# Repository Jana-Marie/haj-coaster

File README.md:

# haj-coaster

A sharky and colourful coaster glowing in pride for you~.

It consists of a stack of three circuit boards, sandwhiched together. There is a STM32F072, a LED driver and plenty LEDs on the baseboard, cutouts on the midboards to hide the components in, and a mask frontboard that shows the artwork. The LEDs are not all simple RGB ones, but a set of single color LEDs for the stars, carefully selected to represent the diversity in color on a night sky. For the girl on the left side, each LED spot consists of 5 single LEDs, RGB + Pink + Cyan, allowing one to expand the typical RGB range with opically pleasant cyan tones (for the shark and drink) and pink tones (e.g. for the skin, shark and drink).
There is also a NTC within the stack, I intended to change the sharks colour from cyan to pink following the coasters temperature. A warm drink would tint the shark pink, a cold one cyan. However, I never dared to place a drink on it, it's just to cute to hide it behind some glass or mug 🥺

<table>
  <tbody>
    <tr>
      <td colspan="2">
        
      </td>
    </tr>
    <tr>
      <td>
        
      </td>
      <td>
        
      </td>
    </tr>
    <tr>
      <td colspan="2">
        
      </td>
    </tr>
    <tr>
      <td>
        
      </td>
      <td>
        
      </td>
    </tr>
    <tr>
      <td colspan="2">
        
      </td>
    </tr>
  </tbody>
</table>

---

### Schematic

(https://github.com/Jana-Marie/haj-coaster/blob/main/coaster_backboard/schematic.pdf)[schematic.pdf]

---

Thank you [かにあじ](https://void-aquarium.com/) for allowing me to use your fantastic artwork for this project! ありがとうございます!

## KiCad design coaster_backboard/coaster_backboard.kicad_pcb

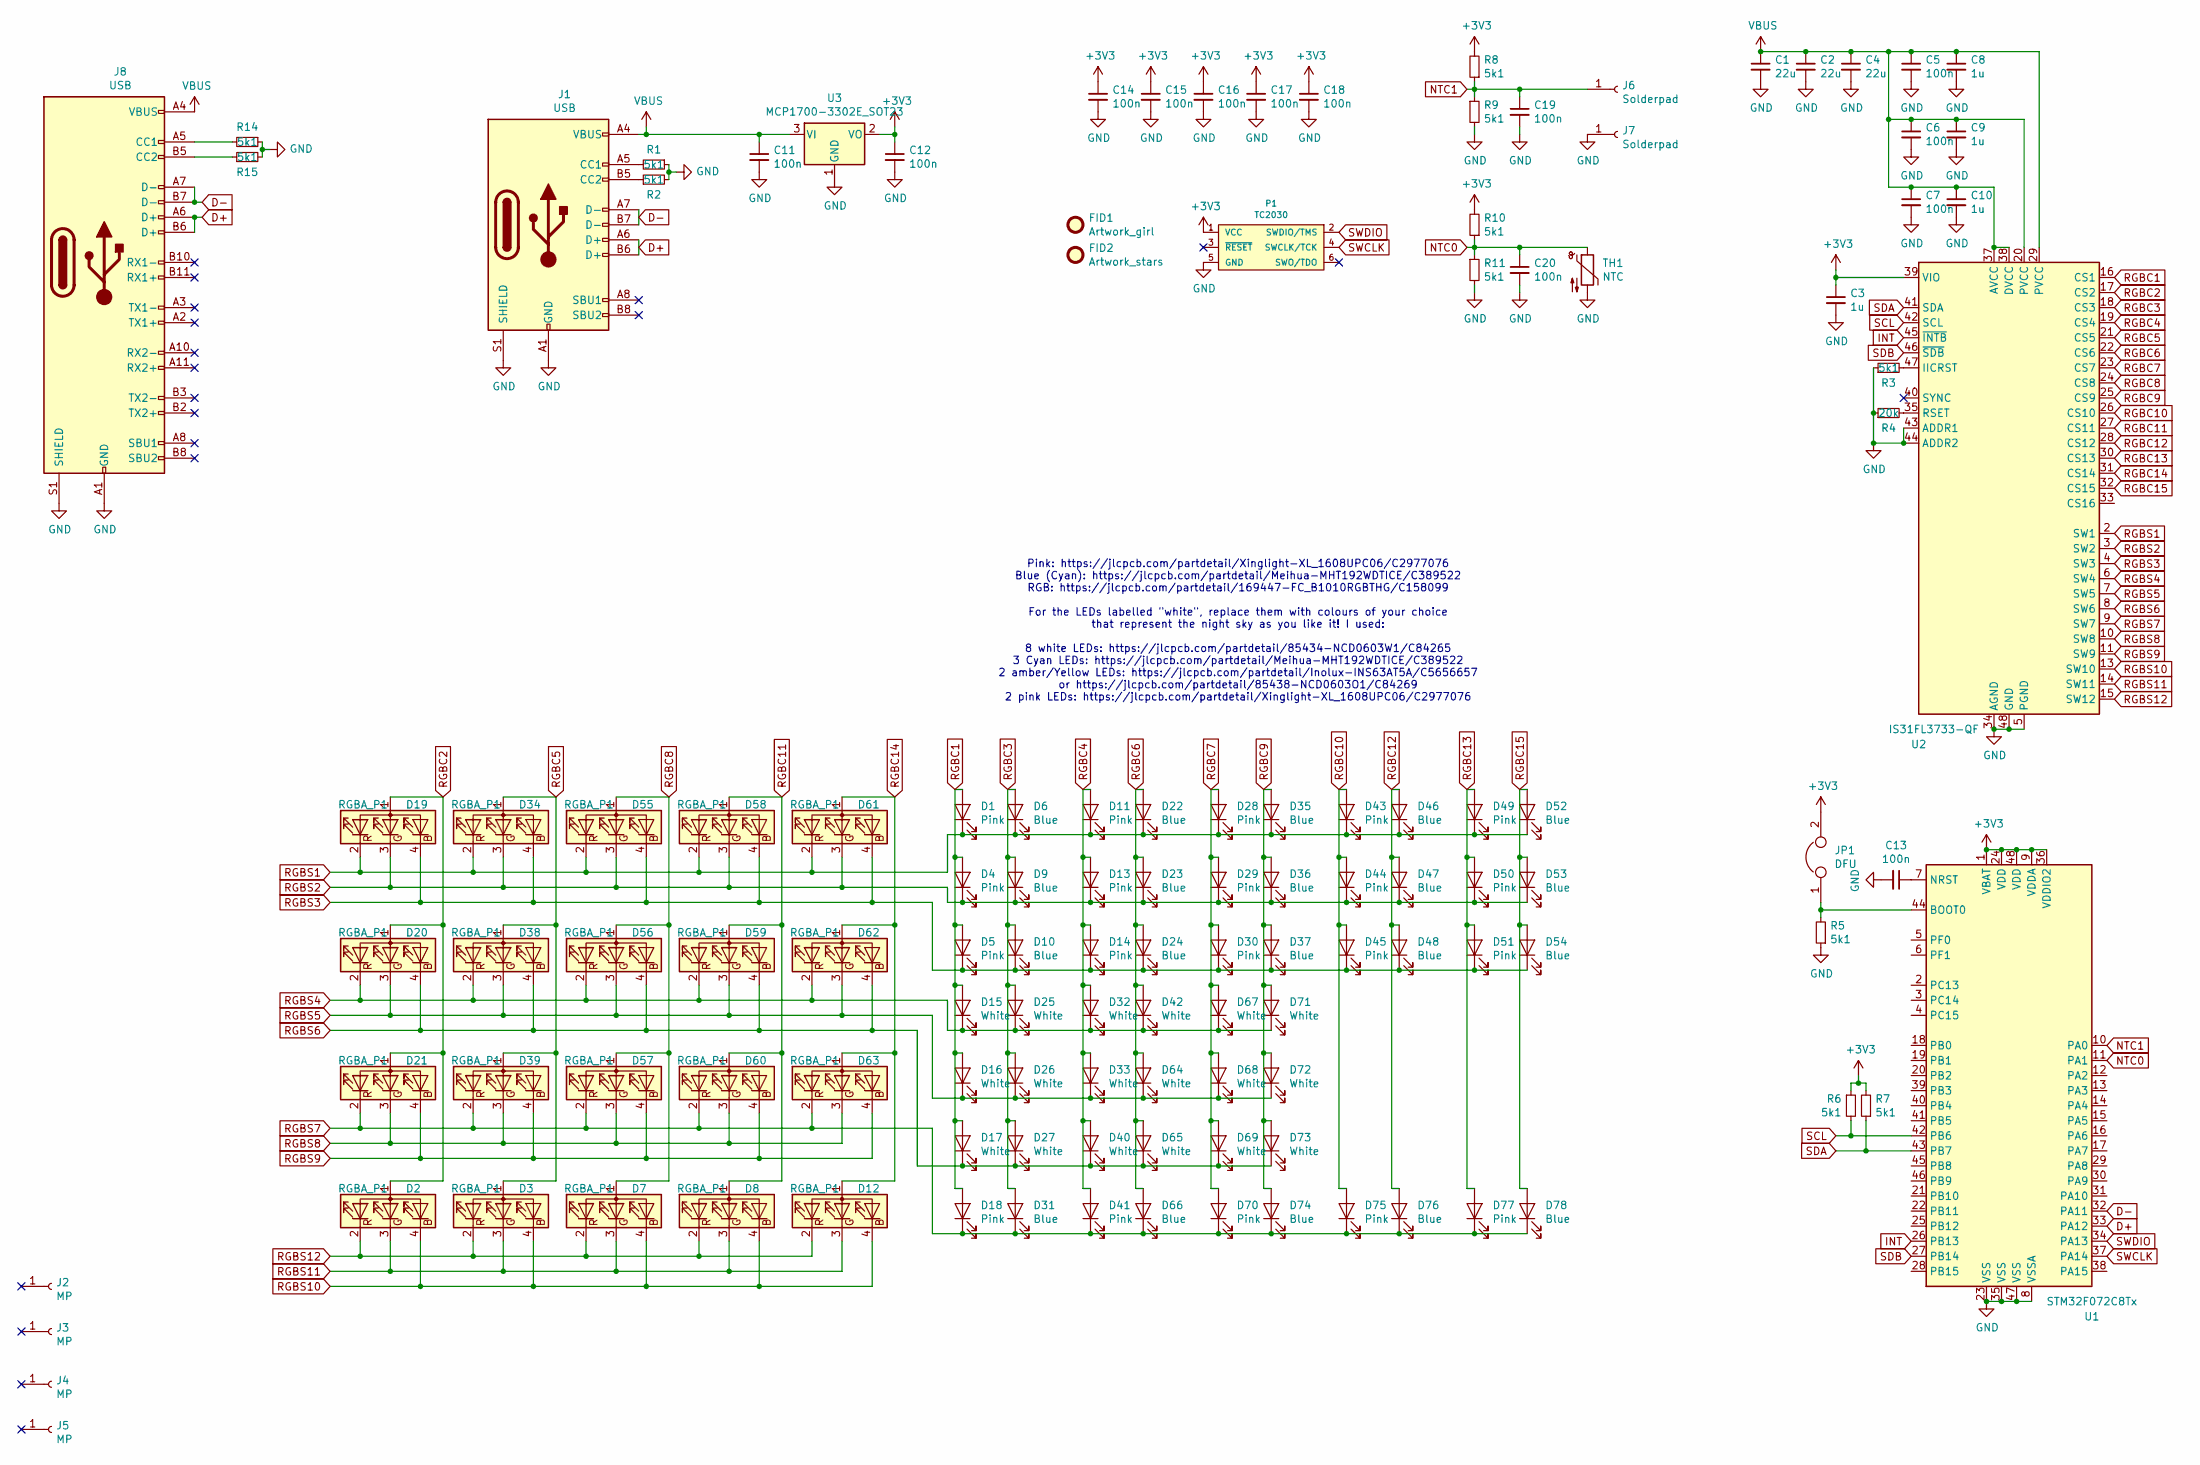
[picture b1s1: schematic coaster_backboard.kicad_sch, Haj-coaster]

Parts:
C1, C2, C4: 22u; C_0805
C3, C8, C9, C10: 1u; C_0603
C5, C6, C7, C11, C12, C13, C14, C15, C16, C17, C18, C19, C20: 100n; C_0402
D1, D4, D5, D11, D13, D14, D18, D28, D29, D30, D41, D43, D44, D45, D49, D50, D51, D70, D75, D77: Pink; LED_0603_1608Metric
D2, D3, D7, D8, D12, D19, D20, D21, D34, D38, D39, D55, D56, D57, D58, D59, D60, D61, D62, D63: RGBA_P1; FC-B1010RGBT-HG
D6, D9, D10, D22, D23, D24, D31, D35, D36, D37, D46, D47, D48, D52, D53, D54, D66, D74, D76, D78: Blue; LED_0603_1608Metric
D15, D16, D17, D25, D26, D27, D32, D33, D40, D42, D64, D65, D67, D68, D69, D71, D72, D73: White; LED_0603_1608Metric
FID1: Artwork_girl; shark_girl_kani_aji_
FID2: Artwork_stars; stars_kani_aji_
J1: USB; USB-C 16Pin InBoard
J2, J3, J4, J5: MP; Pin_D1.0mm_L10.0mm_LooseFit
J6, J7: Solderpad; Pin_D0.7mm_L6.5mm_W1.8mm_FlatFork
J8: USB; 918-418K2022Y40004
JP1: DFU; R_0805
P1: TC2030
R1, R2, R3, R5, R6, R7, R8, R9, R10, R11, R14, R15: 5k1; R_0402
R4: 20k; R_0402
TH1: NTC; R_0603
U1: STM32F072C8Tx; LQFP-48_7x7mm_P0.5mm
U2: IS31FL3733-QF; QFN-48-1EP_6x6mm_P0.4mm_EP4.2x4.2mm
U3: MCP1700-3302E_SOT23; SOT-23

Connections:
+3V3: C3.1, C12.1, C14.1, C15.1, C16.1, C17.1, C18.1, JP1.2, P1.1 (VCC), R6.1, R7.2, R8.2, R10.2, U1.1 (VBAT), U1.9 (VDDA), U1.24 (VDD), U1.36 (VDDIO2), U1.48 (VDD), U2.39 (VIO), U3.2 (VO)
D+: J1.A6 (D+), J1.B6 (D+), J8.A6 (D+), J8.B6 (D+), U1.33 (PA12)
D-: J1.A7 (D-), J1.B7 (D-), J8.A7 (D-), J8.B7 (D-), U1.32 (PA11)
GND: C1.2, C2.2, C3.2, C4.2, C5.2, C6.2, C7.2, C8.2, C9.2, C10.2, C11.2, C12.2, C13.2, C14.2, C15.2, C16.2, C17.2, C18.2, C19.2, C20.2, J1.A1 (GND), J1.A12 (GND), J1.B1 (GND), J1.B12 (GND), J1.S1 (SHIELD), J7.1, J8.A1 (GND), J8.A12 (GND), J8.B1 (GND), J8.B12 (GND), J8.S1 (SHIELD), P1.5 (GND), R1.1, R2.2, R3.1, R4.1, R5.1, R9.2, R11.2, R14.1, R15.2, TH1.2, U1.8 (VSSA), U1.23 (VSS), U1.35 (VSS), U1.47 (VSS), U2.5 (PGND), U2.12 (PGND), U2.34 (AGND), U2.43 (ADDR1), U2.44 (ADDR2), U2.48 (GND), U2.49 (GND), U3.1 (GND)
INT: U1.26 (PB13), U2.45 (~INTB)
NTC0: C20.1, R10.1, R11.1, TH1.1, U1.11 (PA1)
NTC1: C19.1, J6.1, R8.1, R9.1, U1.10 (PA0)
unnamed: C13.1, U1.7 (NRST)
unnamed: J1.A5 (CC1), R1.2
unnamed: J1.B5 (CC2), R2.1
unnamed: J8.A5 (CC1), R14.2
unnamed: J8.B5 (CC2), R15.1
unnamed: JP1.1, R5.2, U1.44 (BOOT0)
unnamed: R3.2, U2.47 (IICRST)
unnamed: R4.2, U2.35 (RSET)
RGBC1: D1.2 (A), D4.2 (A), D5.2 (A), D15.2 (A), D16.2 (A), D17.2 (A), D18.2 (A), U2.16 (CS1)
RGBC2: D2.1 (A), D19.1 (A), D20.1 (A), D21.1 (A), U2.17 (CS2)
RGBC3: D6.2 (A), D9.2 (A), D10.2 (A), D25.2 (A), D26.2 (A), D27.2 (A), D31.2 (A), U2.18 (CS3)
RGBC4: D11.2 (A), D13.2 (A), D14.2 (A), D32.2 (A), D33.2 (A), D40.2 (A), D41.2 (A), U2.19 (CS4)
RGBC5: D3.1 (A), D34.1 (A), D38.1 (A), D39.1 (A), U2.21 (CS5)
RGBC6: D22.2 (A), D23.2 (A), D24.2 (A), D42.2 (A), D64.2 (A), D65.2 (A), D66.2 (A), U2.22 (CS6)
RGBC7: D28.2 (A), D29.2 (A), D30.2 (A), D67.2 (A), D68.2 (A), D69.2 (A), D70.2 (A), U2.23 (CS7)
RGBC8: D7.1 (A), D55.1 (A), D56.1 (A), D57.1 (A), U2.24 (CS8)
RGBC9: D35.2 (A), D36.2 (A), D37.2 (A), D71.2 (A), D72.2 (A), D73.2 (A), D74.2 (A), U2.25 (CS9)
RGBC10: D43.2 (A), D44.2 (A), D45.2 (A), D75.2 (A), U2.26 (CS10)
RGBC11: D8.1 (A), D58.1 (A), D59.1 (A), D60.1 (A), U2.27 (CS11)
RGBC12: D46.2 (A), D47.2 (A), D48.2 (A), D76.2 (A), U2.28 (CS12)
RGBC13: D49.2 (A), D50.2 (A), D51.2 (A), D77.2 (A), U2.30 (CS13)
RGBC14: D12.1 (A), D61.1 (A), D62.1 (A), D63.1 (A), U2.31 (CS14)
RGBC15: D52.2 (A), D53.2 (A), D54.2 (A), D78.2 (A), U2.32 (CS15)
RGBS1: D1.1 (K), D6.1 (K), D11.1 (K), D19.2 (RK), D22.1 (K), D28.1 (K), D34.2 (RK), D35.1 (K), D43.1 (K), D46.1 (K), D49.1 (K), D52.1 (K), D55.2 (RK), D58.2 (RK), D61.2 (RK), U2.2 (SW1)
RGBS2: D4.1 (K), D9.1 (K), D13.1 (K), D19.3 (GK), D23.1 (K), D29.1 (K), D34.3 (GK), D36.1 (K), D44.1 (K), D47.1 (K), D50.1 (K), D53.1 (K), D55.3 (GK), D58.3 (GK), D61.3 (GK), U2.3 (SW2)
RGBS3: D5.1 (K), D10.1 (K), D14.1 (K), D19.4 (BK), D24.1 (K), D30.1 (K), D34.4 (BK), D37.1 (K), D45.1 (K), D48.1 (K), D51.1 (K), D54.1 (K), D55.4 (BK), D58.4 (BK), D61.4 (BK), U2.4 (SW3)
RGBS4: D15.1 (K), D20.2 (RK), D25.1 (K), D32.1 (K), D38.2 (RK), D42.1 (K), D56.2 (RK), D59.2 (RK), D62.2 (RK), D67.1 (K), D71.1 (K), U2.6 (SW4)
RGBS5: D16.1 (K), D20.3 (GK), D26.1 (K), D33.1 (K), D38.3 (GK), D56.3 (GK), D59.3 (GK), D62.3 (GK), D64.1 (K), D68.1 (K), D72.1 (K), U2.7 (SW5)
RGBS6: D17.1 (K), D20.4 (BK), D27.1 (K), D38.4 (BK), D40.1 (K), D56.4 (BK), D59.4 (BK), D62.4 (BK), D65.1 (K), D69.1 (K), D73.1 (K), U2.8 (SW6)
RGBS7: D18.1 (K), D21.2 (RK), D31.1 (K), D39.2 (RK), D41.1 (K), D57.2 (RK), D60.2 (RK), D63.2 (RK), D66.1 (K), D70.1 (K), D74.1 (K), D75.1 (K), D76.1 (K), D77.1 (K), D78.1 (K), U2.9 (SW7)
RGBS8: D21.3 (GK), D39.3 (GK), D57.3 (GK), D60.3 (GK), D63.3 (GK), U2.10 (SW8)
RGBS9: D21.4 (BK), D39.4 (BK), D57.4 (BK), D60.4 (BK), D63.4 (BK), U2.11 (SW9)
RGBS10: D2.4 (BK), D3.4 (BK), D7.4 (BK), D8.4 (BK), D12.4 (BK), U2.13 (SW10)
RGBS11: D2.3 (GK), D3.3 (GK), D7.3 (GK), D8.3 (GK), D12.3 (GK), U2.14 (SW11)
RGBS12: D2.2 (RK), D3.2 (RK), D7.2 (RK), D8.2 (RK), D12.2 (RK), U2.15 (SW12)
SCL: R6.2, U1.42 (PB6), U2.42 (SCL)
SDA: R7.1, U1.43 (PB7), U2.41 (SDA)
SDB: U1.27 (PB14), U2.46 (~SDB)
SWCLK: P1.4 (SWCLK/TCK), U1.37 (PA14)
SWDIO: P1.2 (SWDIO/TMS), U1.34 (PA13)
VBUS: C1.1, C2.1, C4.1, C5.1, C6.1, C7.1, C8.1, C9.1, C10.1, C11.1, J1.A4 (VBUS), J1.A9 (VBUS), J1.B4 (VBUS), J1.B9 (VBUS), J8.A4 (VBUS), J8.A9 (VBUS), J8.B4 (VBUS), J8.B9 (VBUS), U2.20 (PVCC), U2.29 (PVCC), U2.37 (AVCC), U2.38 (DVCC), U3.3 (VI)

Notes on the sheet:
Pink: https://jlcpcb.com/partdetail/Xinglight-XL_1608UPC06/C2977076 Blue (Cyan): https://jlcpcb.com/partdetail/Meihua-MHT192WDTICE/C389522 RGB: https://jlcpcb.com/partdetail/169447-FC_B1010RGBTHG/C158099 For the LEDs labelled "white", replace them with colours of your choice that represent the nigh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

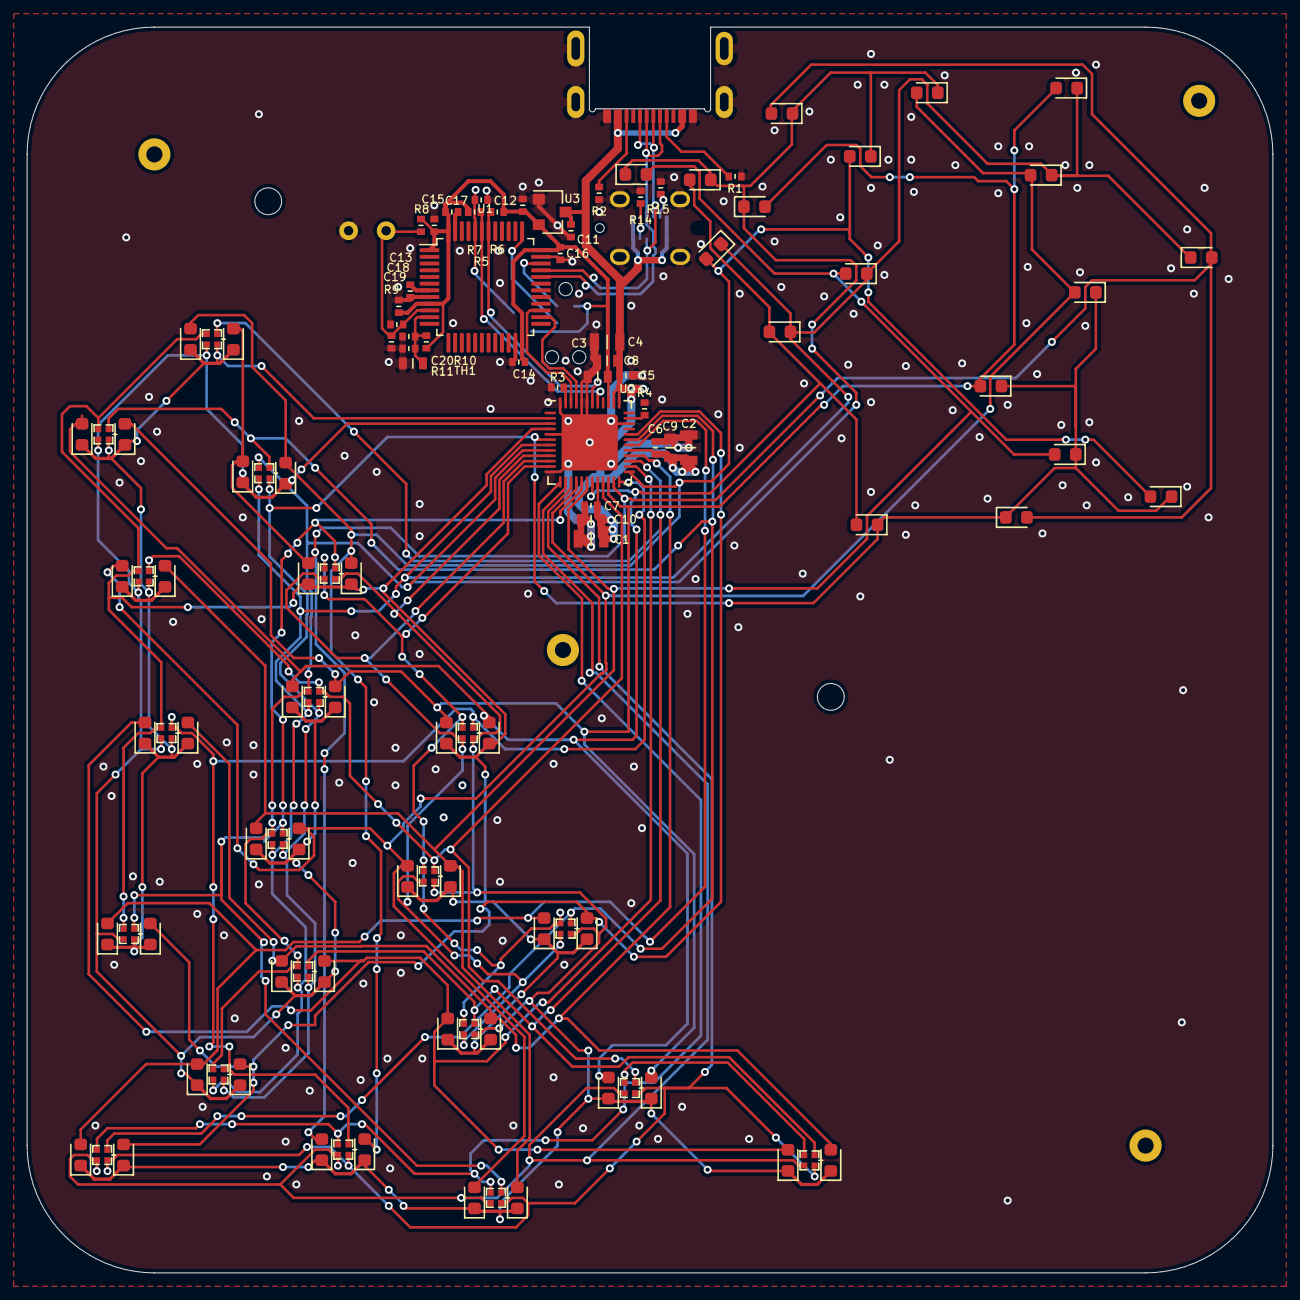
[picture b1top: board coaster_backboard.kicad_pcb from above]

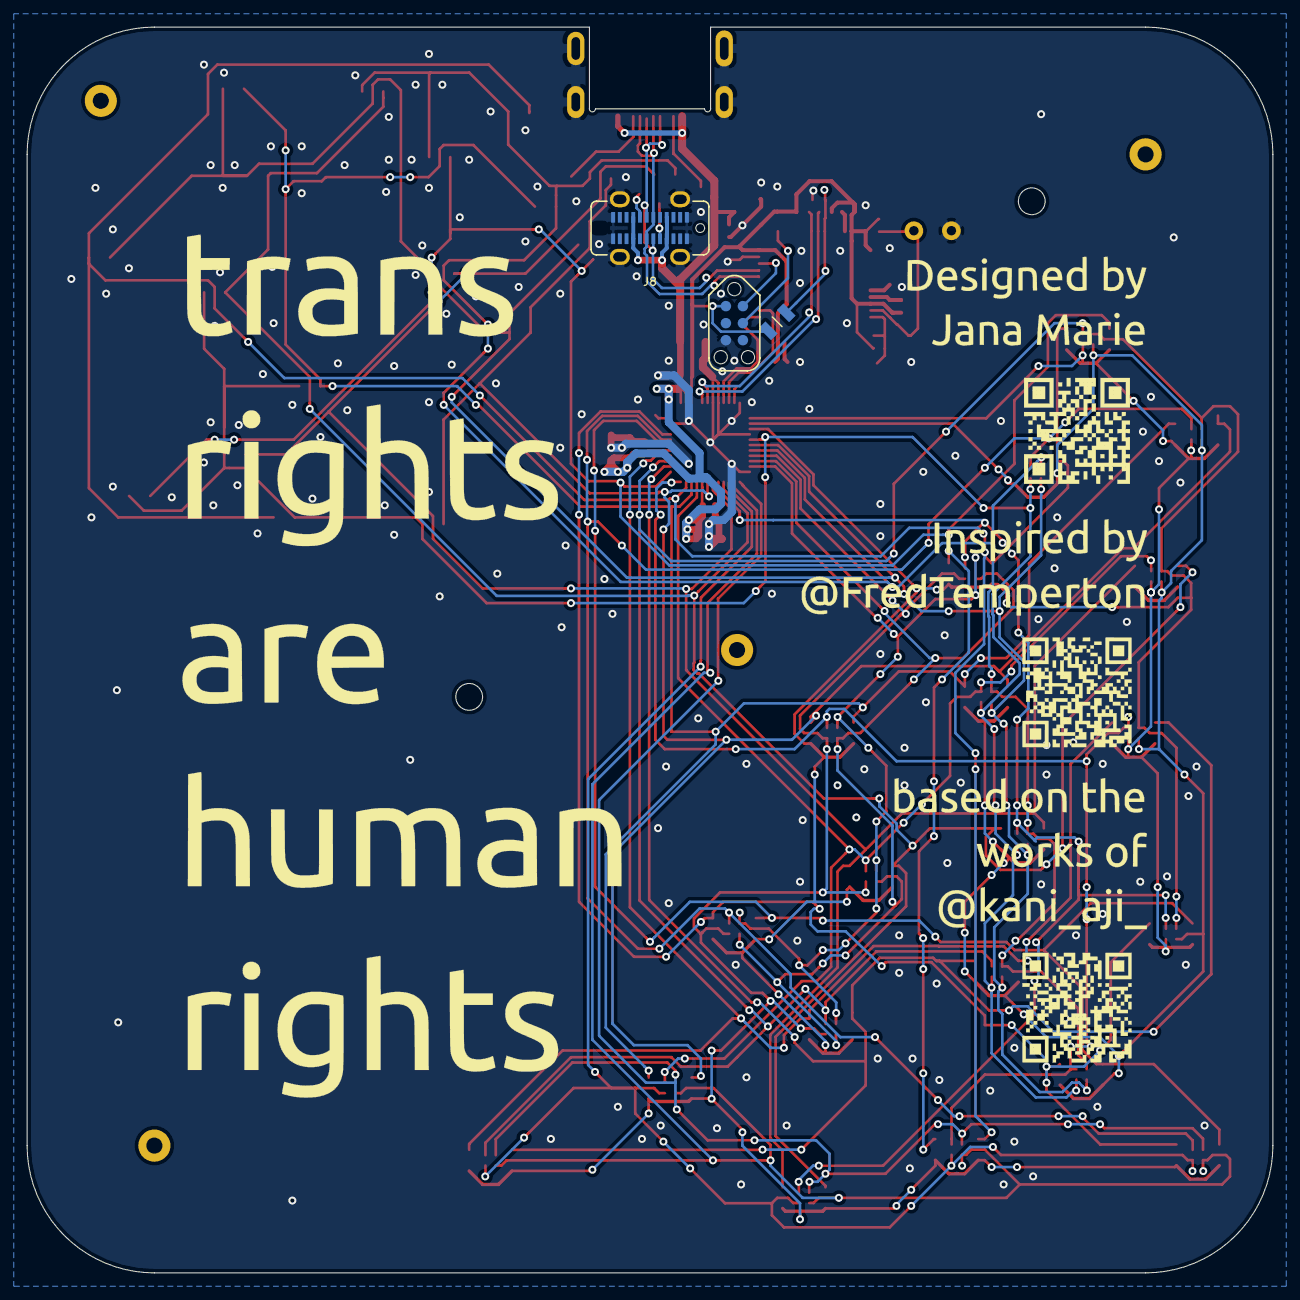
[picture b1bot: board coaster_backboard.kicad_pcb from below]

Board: 2 copper layers, 93.0 x 93.0 mm, 127 parts (5 on the bottom side), 48 nets.

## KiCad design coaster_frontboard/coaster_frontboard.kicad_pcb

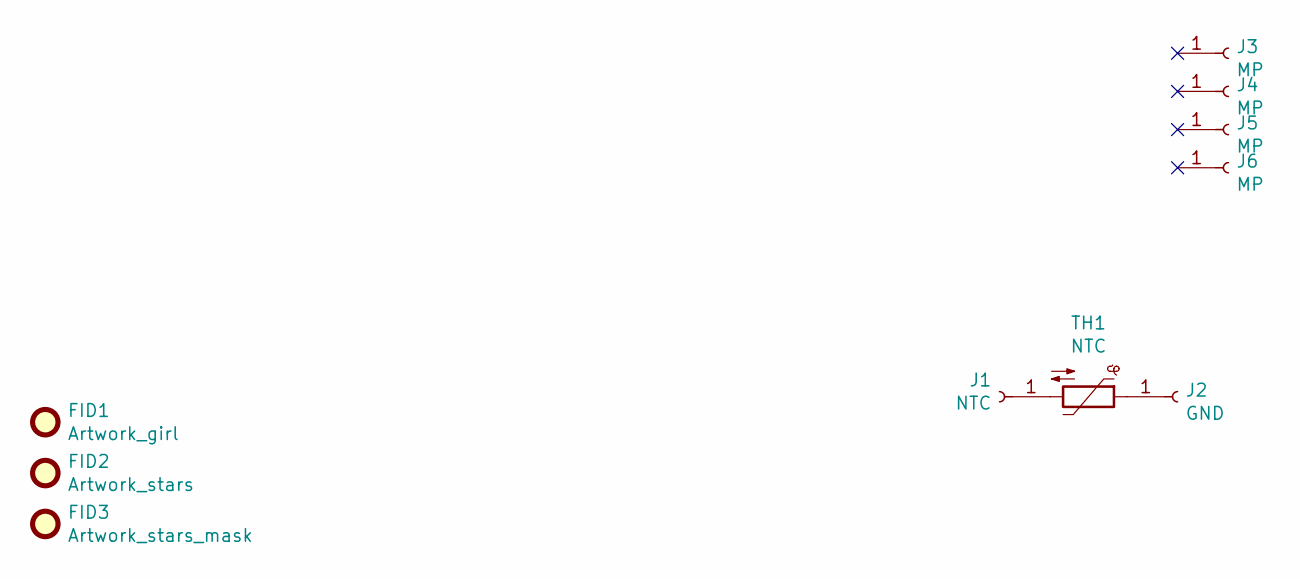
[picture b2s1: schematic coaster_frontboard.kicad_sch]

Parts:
FID1: Artwork_girl; shark_girl_kani_aji_
FID2: Artwork_stars; stars_kani_aji_
FID3: Artwork_stars_mask; stars_mask_kani_aji_
J1: NTC; TestPoint_Pad_D1.5mm
J2: GND; TestPoint_Pad_D1.5mm
J3, J4, J5, J6: MP; TestPoint_Pad_D1.5mm
TH1: NTC; R_0402

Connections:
unnamed: J1.1, TH1.2
unnamed: J2.1, TH1.1

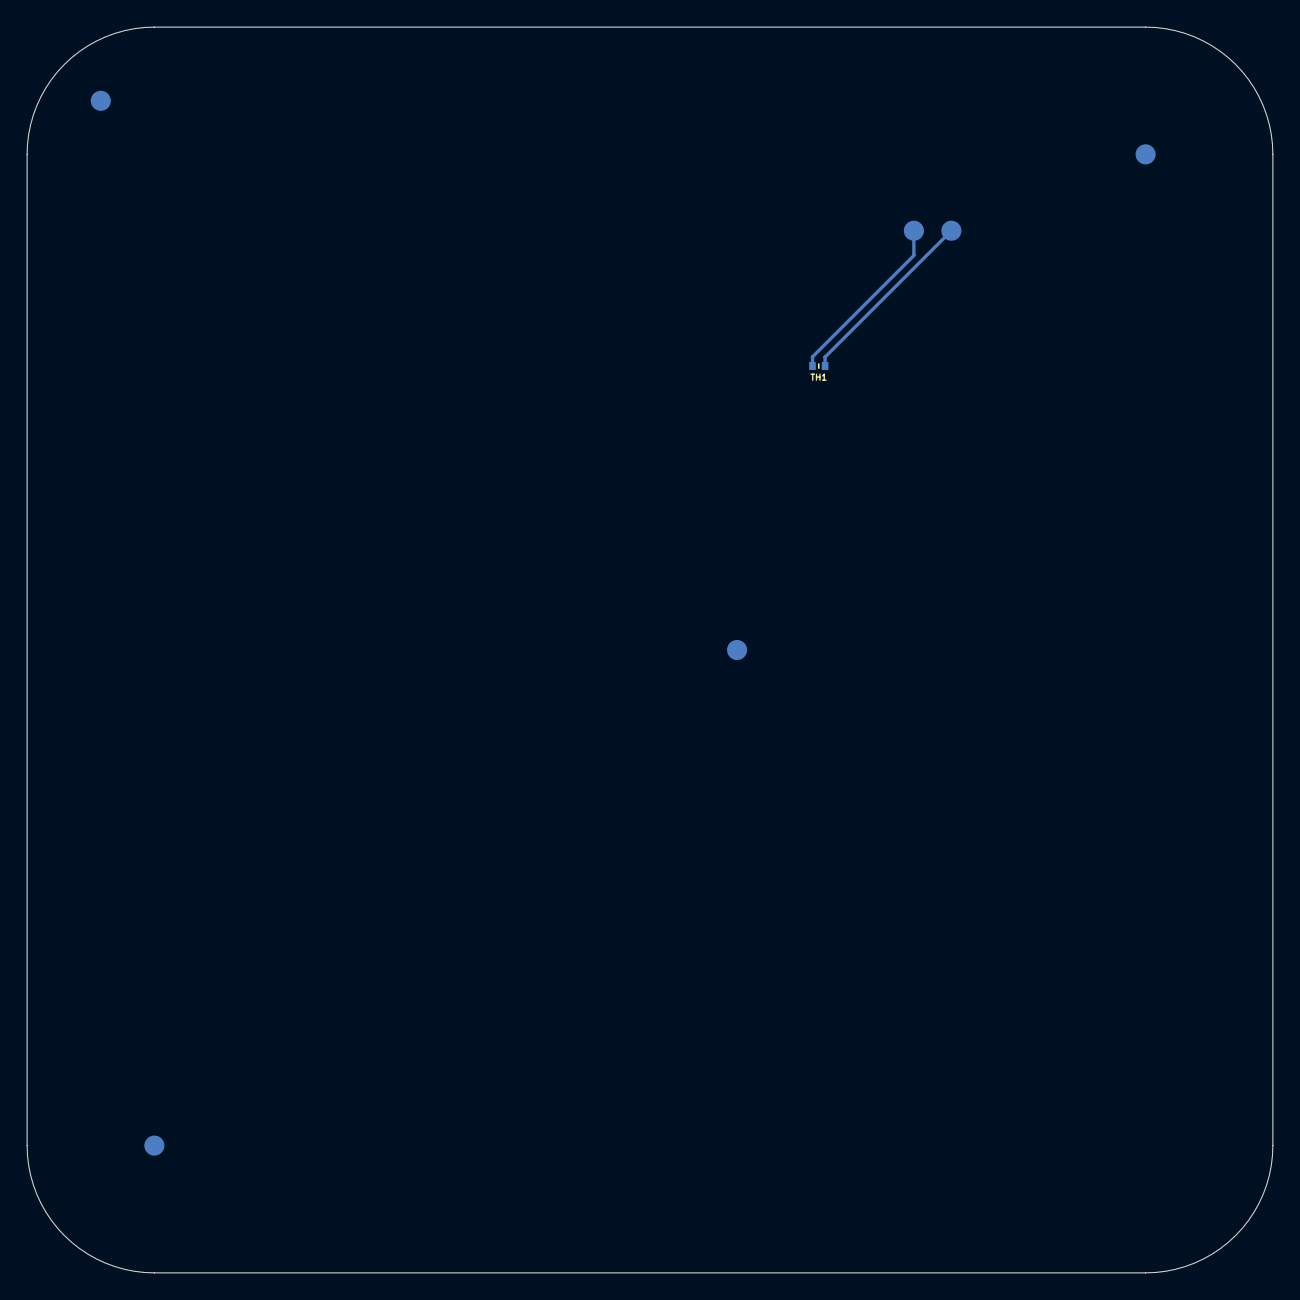
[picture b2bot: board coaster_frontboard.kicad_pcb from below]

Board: 2 copper layers, 93.0 x 93.0 mm, 10 parts (7 on the bottom side), 2 nets.

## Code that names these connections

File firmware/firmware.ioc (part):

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Mcu.Name=STM32F072C(8-B)Tx
Mcu.Package=LQFP48
Mcu.UserName=STM32F072C8Tx
PA0.GPIOParameters=GPIO_Label
PA0.GPIO_Label=NTC1
PA0.Mode=IN0
PA0.Signal=ADC_IN0
PA1.GPIOParameters=GPIO_Label
PA1.GPIO_Label=NTC0
PA1.Mode=IN1
PA1.Signal=ADC_IN1
PA11.Mode=Device
PA11.Signal=USB_DM
PA12.Mode=Device
PA12.Signal=USB_DP
PA13.Mode=Serial_Wire
PA13.Signal=SYS_SWDIO
PA14.Mode=Serial_Wire
PA14.Signal=SYS_SWCLK
PB13.GPIOParameters=GPIO_Label
PB13.GPIO_Label=INT
PB13.Signal=GPXTI13
PB14.GPIOParameters=GPIO_Label
PB14.GPIO_Label=EN
PB14.Signal=GPIO_Output
PB6.Mode=I2C
PB6.Signal=I2C1_SCL
PB7.Mode=I2C
PB7.Signal=I2C1_SDA
RCC.SYSCLKFreq_VALUE=48000000
RCC.SYSCLKSource=RCC_SYSCLKSOURCE_HSI48
board=custom

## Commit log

2021-10-21 added backboard
2021-10-21 added frontboard
2021-10-21 added midboard
2021-10-21 added artwork files
2021-10-21 routing 80%
2023-04-21 updated gitignore
2023-04-21 updated hw
2023-04-21 added fw
2023-04-21 added artwork
2023-04-21 updated midboard
2023-04-21 added images
2023-08-02 updated gitignore, added FW
2023-08-02 updated backboard
2023-08-02 updated frontboard
2023-08-03 removed jdebug file
2023-08-03 added more images
2023-08-03 fixed typo
2023-09-30 added schematic print
2025-04-08 updated schematic
